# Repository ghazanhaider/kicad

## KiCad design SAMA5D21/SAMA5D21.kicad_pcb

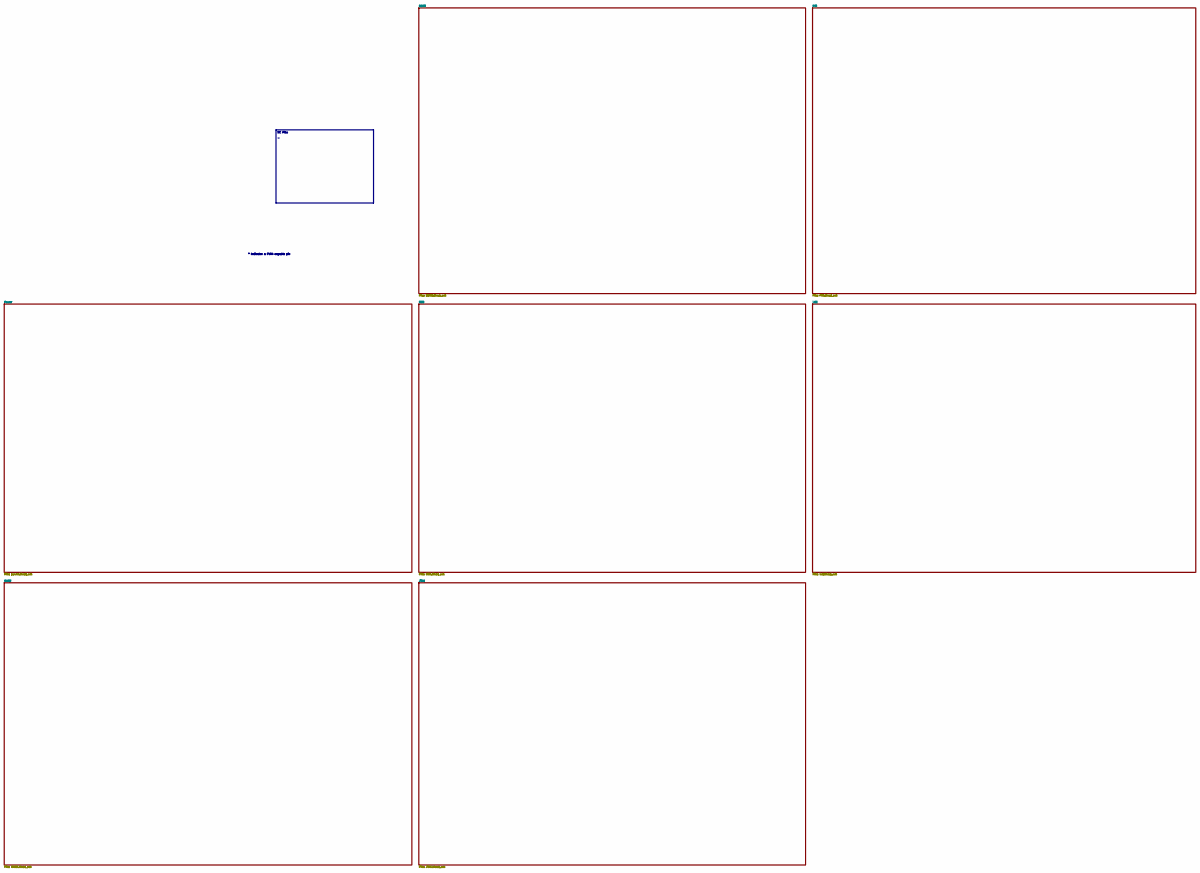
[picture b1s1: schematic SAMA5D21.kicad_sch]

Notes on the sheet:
NC Pins -
* Indicates a PWM-capable pin

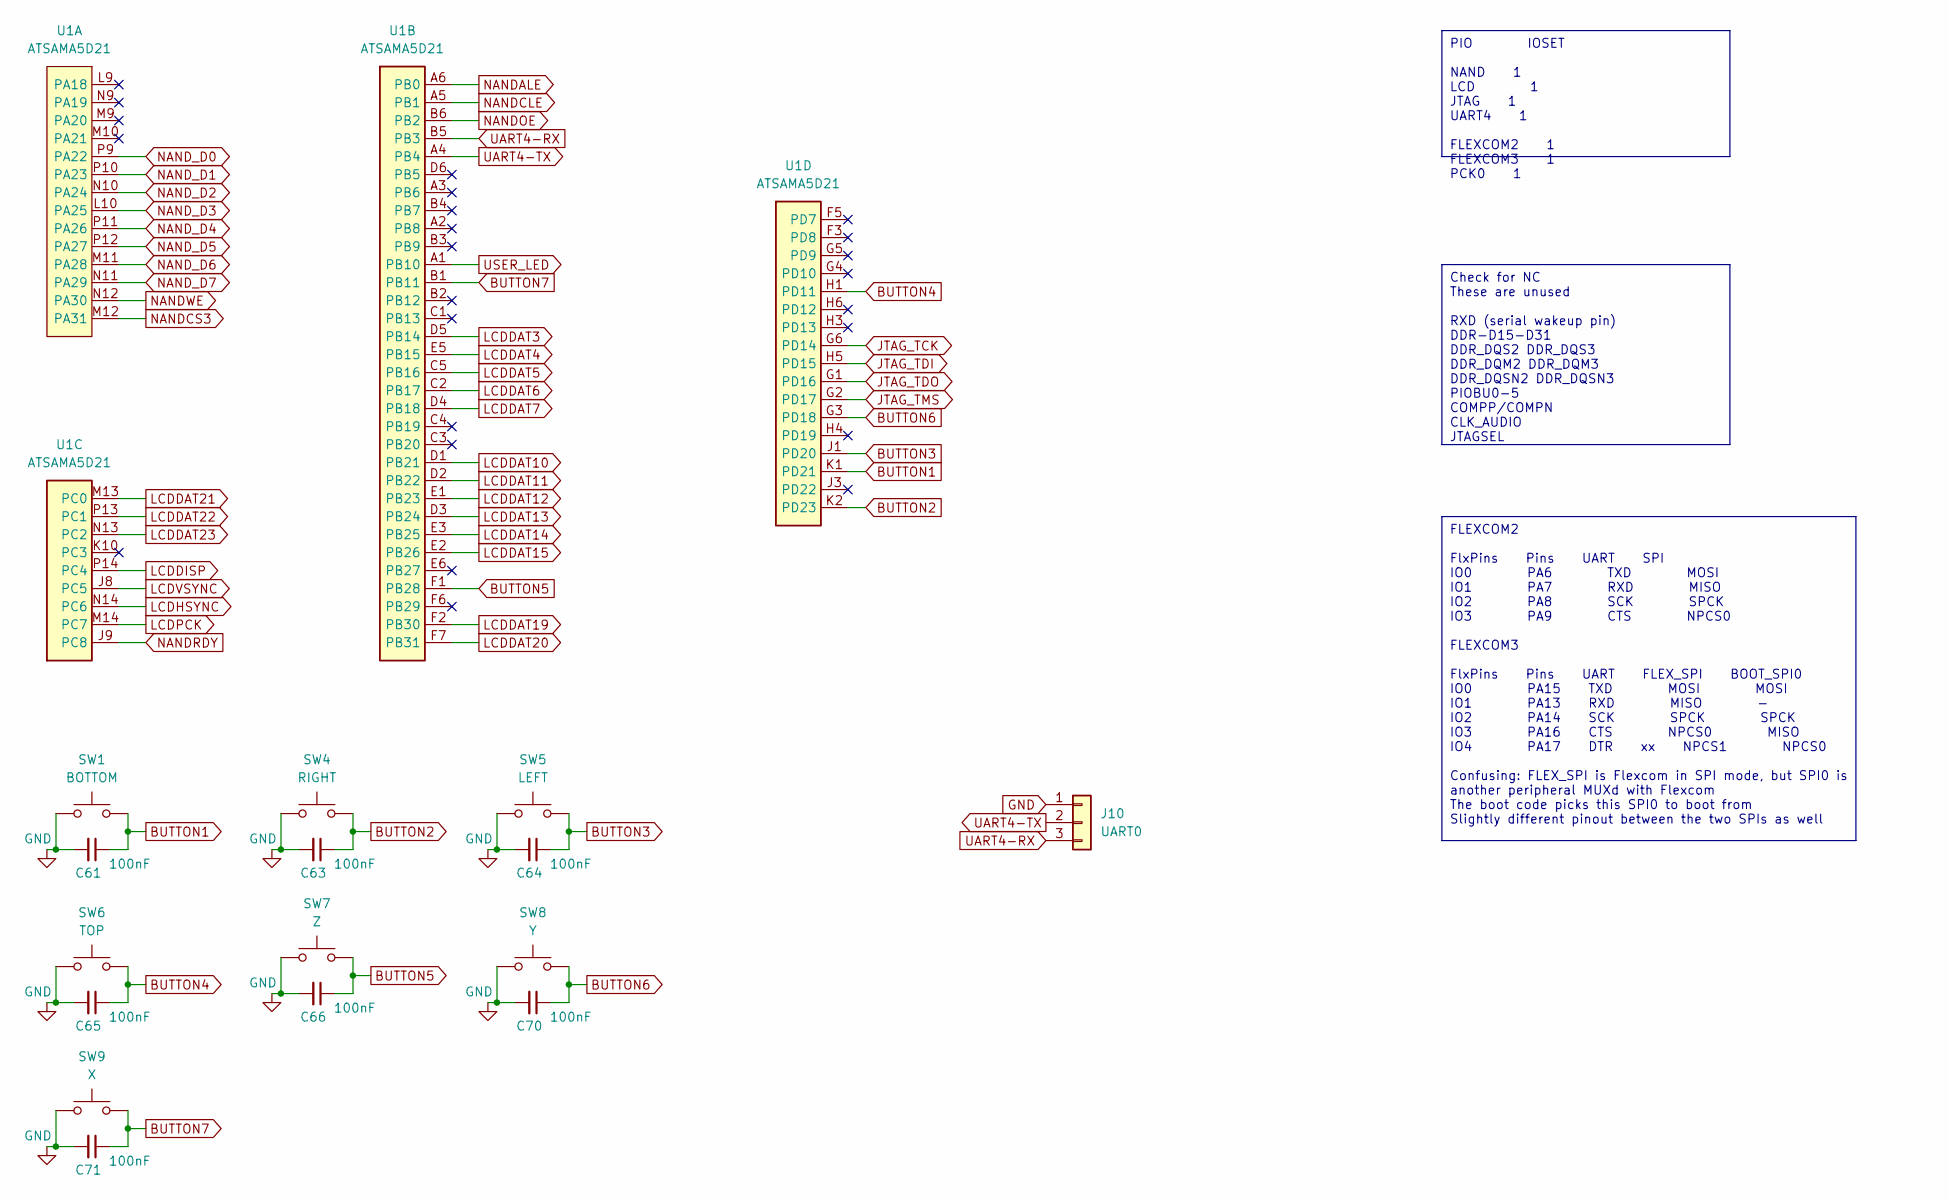
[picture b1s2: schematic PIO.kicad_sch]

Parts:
C61, C63, C64, C65, C66, C70, C71: 100nF; C_0603_1608Metric
J10: UART0; PinHeader_1x03_P1.27mm_Vertical
SW1: BOTTOM; SW_SPST_TL3305A
SW4: RIGHT; SW_SPST_TL3305A
SW5: LEFT; SW_SPST_TL3305A
SW6: TOP; SW_SPST_TL3305A
SW7: Z; SW_SPST_TL3305A
SW8: Y; SW_SPST_TL3305A
SW9: X; SW_SPST_TL3305A
U1: ATSAMA5D21; Microchip_TFBGA-196_11x11mm_Layout14x14_P0.75mm_SMD

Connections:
BUTTON1: C61.1, SW1.2, U1.K1 (PD21)
BUTTON2: C63.1, SW4.2, U1.K2 (PD23)
BUTTON3: C64.1, SW5.2, U1.J1 (PD20)
BUTTON4: C65.1, SW6.2, U1.H1 (PD11)
BUTTON5: C66.1, SW7.2, U1.F1 (PB28)
BUTTON6: C70.1, SW8.2, U1.G3 (PD18)
BUTTON7: C71.1, SW9.2, U1.B1 (PB11)
GNDADIOPLL: C61.2, C63.2, C64.2, C65.2, C66.2, C70.2, C71.2, J10.1, SW1.1, SW4.1, SW5.1, SW6.1, SW7.1, SW8.1, SW9.1; also elsewhere on the board
JTAG_TCK: U1.G6 (PD14); also elsewhere on the board
JTAG_TDI: U1.H5 (PD15); also elsewhere on the board
JTAG_TDO: U1.G1 (PD16); also elsewhere on the board
JTAG_TMS: U1.G2 (PD17); also elsewhere on the board
LCDDAT3: U1.D5 (PB14); also elsewhere on the board
LCDDAT4: U1.E5 (PB15); also elsewhere on the board
LCDDAT5: U1.C5 (PB16); also elsewhere on the board
LCDDAT6: U1.C2 (PB17); also elsewhere on the board
LCDDAT7: U1.D4 (PB18); also elsewhere on the board
LCDDAT10: U1.D1 (PB21); also elsewhere on the board
LCDDAT11: U1.D2 (PB22); also elsewhere on the board
LCDDAT12: U1.E1 (PB23); also elsewhere on the board
LCDDAT13: U1.D3 (PB24); also elsewhere on the board
LCDDAT14: U1.E3 (PB25); also elsewhere on the board
LCDDAT15: U1.E2 (PB26); also elsewhere on the board
LCDDAT19: U1.F2 (PB30); also elsewhere on the board
LCDDAT20: U1.F7 (PB31); also elsewhere on the board
LCDDAT21: U1.M13 (PC0); also elsewhere on the board
LCDDAT22: U1.P13 (PC1); also elsewhere on the board
LCDDAT23: U1.N13 (PC2); also elsewhere on the board
LCDDISP: U1.P14 (PC4); also elsewhere on the board
LCDHSYNC: U1.N14 (PC6); also elsewhere on the board
LCDPCK: U1.M14 (PC7); also elsewhere on the board
LCDVSYNC: U1.J8 (PC5); also elsewhere on the board
NANDALE: U1.A6 (PB0); also elsewhere on the board
NANDCLE: U1.A5 (PB1); also elsewhere on the board
NANDCS3: U1.M12 (PA31); also elsewhere on the board
NANDOE: U1.B6 (PB2); also elsewhere on the board
NANDRDY: U1.J9 (PC8); also elsewhere on the board
NANDWE: U1.N12 (PA30); also elsewhere on the board
NAND_D0: U1.P9 (PA22); also elsewhere on the board
NAND_D1: U1.P10 (PA23); also elsewhere on the board
NAND_D2: U1.N10 (PA24); also elsewhere on the board
NAND_D3: U1.L10 (PA25); also elsewhere on the board
NAND_D4: U1.P11 (PA26); also elsewhere on the board
NAND_D5: U1.P12 (PA27); also elsewhere on the board
NAND_D6: U1.M11 (PA28); also elsewhere on the board
NAND_D7: U1.N11 (PA29); also elsewhere on the board
UART4-RX: J10.3, U1.B5 (PB3)
UART4-TX: J10.2, U1.A4 (PB4)
USER_LED: U1.A1 (PB10); also elsewhere on the board

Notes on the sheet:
PIO IOSET NAND 1 LCD 1 JTAG 1 UART4 1 FLEXCOM2 1 FLEXCOM3 1 PCK0 1
Check for NC These are unused RXD (serial wakeup pin) DDR-D15-D31 DDR_DQS2 DDR_DQS3 DDR_DQM2 DDR_DQM3 DDR_DQSN2 DDR_DQSN3 PIOBU0-5 COMPP/COMPN CLK_AUDIO JTAGSEL
FLEXCOM2 FlxPins Pins UART SPI IO0 PA6 TXD MOSI IO1 PA7 RXD MISO IO2 PA8 SCK SPCK IO3 PA9 CTS NPCS0 FLEXCOM3 FlxPins Pins UART FLEX_SPI BOOT_SPI0 IO0 PA15 TXD MOSI MOSI IO1 PA13 RXD MISO - IO2 PA14 SCK SPCK SPCK IO3 PA16 CTS NPCS0 MISO IO4 PA17 DTR xx NPCS1 NPCS0 Confusing: FLEX_SPI is Flexcom in S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

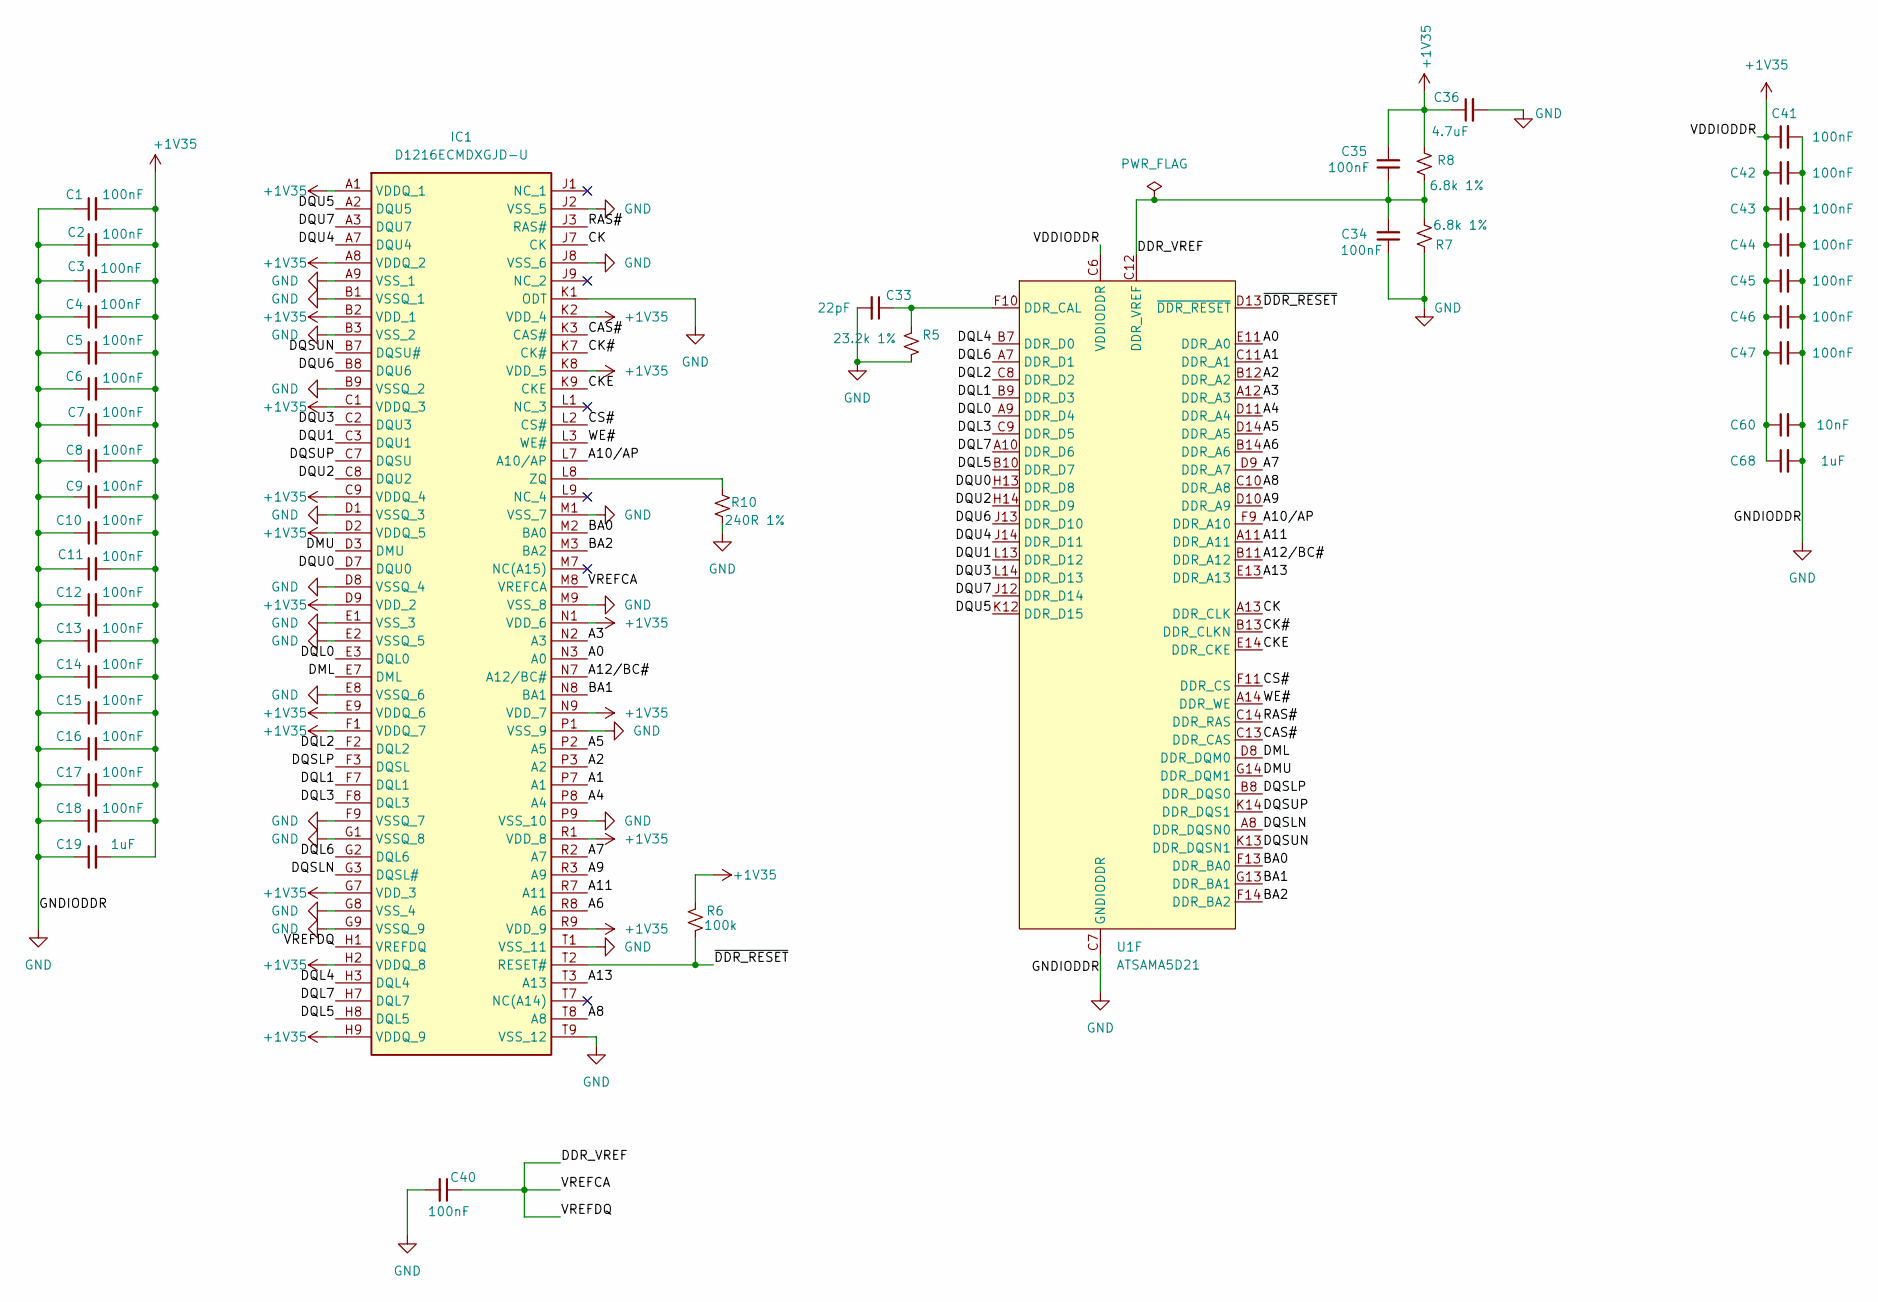
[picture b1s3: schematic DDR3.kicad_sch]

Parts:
C1, C2, C3, C4, C5, C6, C7, C8, C9, C10, C11, C12, C13, C14, C15, C16, C17, C18, C41, C42, C43, C44, C45, C46, C47: 100nF; C_0201_0603Metric
C19, C68: 1uF; C_0603_1608Metric
C33: 22pF; C_0603_1608Metric
C34, C35, C40: 100nF; C_0603_1608Metric
C36: 4.7uF; C_0603_1608Metric
C60: 10nF; C_0201_0603Metric
IC1: D1216ECMDXGJD-U; Micron_FBGA-96_7.5x13.5mm_Layout9x16_P0.8mm; Mouser Part Number D1216ECMDXGJD-U
R5: 23.2k 1%; R_0603_1608Metric
R6: 100k; R_0603_1608Metric
R7, R8: 6.8k 1%; R_0603_1608Metric
R10: 240R 1%; R_0402_1005Metric
U1: ATSAMA5D21; Microchip_TFBGA-196_11x11mm_Layout14x14_P0.75mm_SMD

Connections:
+1V35: C1.2, C2.2, C3.2, C4.2, C5.2, C6.2, C7.2, C8.2, C9.2, C10.2, C11.2, C12.2, C13.2, C14.2, C15.2, C16.2, C17.2, C18.2, C19.2, C35.2, C36.1, C41.1, C42.1, C43.1, C44.1, C45.1, C46.1, C47.1, C60.1, C68.1, IC1.A1 (VDDQ_1), IC1.A8 (VDDQ_2), IC1.B2 (VDD_1), IC1.C1 (VDDQ_3), IC1.C9 (VDDQ_4), IC1.D2 (VDDQ_5), IC1.D9 (VDD_2), IC1.E9 (VDDQ_6), IC1.F1 (VDDQ_7), IC1.G7 (VDD_3), IC1.H2 (VDDQ_8), IC1.H9 (VDDQ_9), IC1.K2 (VDD_4), IC1.K8 (VDD_5), IC1.N1 (VDD_6), IC1.N9 (VDD_7), IC1.R1 (VDD_8), IC1.R9 (VDD_9), R6.2, R8.1, U1.C6 (VDDIODDR), U1.E10 (VDDIODDR), U1.E12 (VDDIODDR), U1.G10 (VDDIODDR), U1.G12 (VDDIODDR), U1.H11 (VDDIODDR), U1.J10 (VDDIODDR); also elsewhere on the board
/DDR3/A0: IC1.N3 (A0), U1.E11 (DDR_A0)
/DDR3/A1: IC1.P7 (A1), U1.C11 (DDR_A1)
/DDR3/A2: IC1.P3 (A2), U1.B12 (DDR_A2)
/DDR3/A3: IC1.N2 (A3), U1.A12 (DDR_A3)
/DDR3/A4: IC1.P8 (A4), U1.D11 (DDR_A4)
/DDR3/A5: IC1.P2 (A5), U1.D14 (DDR_A5)
/DDR3/A6: IC1.R8 (A6), U1.B14 (DDR_A6)
/DDR3/A7: IC1.R2 (A7), U1.D9 (DDR_A7)
/DDR3/A8: IC1.T8 (A8), U1.C10 (DDR_A8)
/DDR3/A9: IC1.R3 (A9), U1.D10 (DDR_A9)
/DDR3/A10/AP: IC1.L7 (A10/AP), U1.F9 (DDR_A10)
/DDR3/A11: IC1.R7 (A11), U1.A11 (DDR_A11)
/DDR3/A12/BC#: IC1.N7 (A12/BC#), U1.B11 (DDR_A12)
/DDR3/A13: IC1.T3 (A13), U1.E13 (DDR_A13)
/DDR3/BA0: IC1.M2 (BA0), U1.F13 (DDR_BA0)
/DDR3/BA1: IC1.N8 (BA1), U1.G13 (DDR_BA1)
/DDR3/BA2: IC1.M3 (BA2), U1.F14 (DDR_BA2)
/DDR3/CAS#: IC1.K3 (CAS#), U1.C13 (DDR_CAS)
/DDR3/CK: IC1.J7 (CK), U1.A13 (DDR_CLK)
/DDR3/CK#: IC1.K7 (CK#), U1.B13 (DDR_CLKN)
/DDR3/CKE: IC1.K9 (CKE), U1.E14 (DDR_CKE)
/DDR3/CS#: IC1.L2 (CS#), U1.F11 (DDR_CS)
/DDR3/DDR_VREF: C34.2, C35.1, C40.1, IC1.H1 (VREFDQ), IC1.M8 (VREFCA), R7.1, R8.2, U1.C12 (DDR_VREF), U1.H12 (DDR_VREF)
/DDR3/DML: IC1.E7 (DML), U1.D8 (DDR_DQM0)
/DDR3/DMU: IC1.D3 (DMU), U1.G14 (DDR_DQM1)
/DDR3/DQL0: IC1.E3 (DQL0), U1.A9 (DDR_D4)
/DDR3/DQL1: IC1.F7 (DQL1), U1.B9 (DDR_D3)
/DDR3/DQL2: IC1.F2 (DQL2), U1.C8 (DDR_D2)
/DDR3/DQL3: IC1.F8 (DQL3), U1.C9 (DDR_D5)
/DDR3/DQL4: IC1.H3 (DQL4), U1.B7 (DDR_D0)
/DDR3/DQL5: IC1.H8 (DQL5), U1.B10 (DDR_D7)
/DDR3/DQL6: IC1.G2 (DQL6), U1.A7 (DDR_D1)
/DDR3/DQL7: IC1.H7 (DQL7), U1.A10 (DDR_D6)
/DDR3/DQSLN: IC1.G3 (DQSL#), U1.A8 (DDR_DQSN0)
/DDR3/DQSLP: IC1.F3 (DQSL), U1.B8 (DDR_DQS0)
/DDR3/DQSUN: IC1.B7 (DQSU#), U1.K13 (DDR_DQSN1)
/DDR3/DQSUP: IC1.C7 (DQSU), U1.K14 (DDR_DQS1)
/DDR3/DQU0: IC1.D7 (DQU0), U1.H13 (DDR_D8)
/DDR3/DQU1: IC1.C3 (DQU1), U1.L13 (DDR_D12)
/DDR3/DQU2: IC1.C8 (DQU2), U1.H14 (DDR_D9)
/DDR3/DQU3: IC1.C2 (DQU3), U1.L14 (DDR_D13)
/DDR3/DQU4: IC1.A7 (DQU4), U1.J14 (DDR_D11)
/DDR3/DQU5: IC1.A2 (DQU5), U1.K12 (DDR_D15)
/DDR3/DQU6: IC1.B8 (DQU6), U1.J13 (DDR_D10)
/DDR3/DQU7: IC1.A3 (DQU7), U1.J12 (DDR_D14)
/DDR3/RAS#: IC1.J3 (RAS#), U1.C14 (DDR_RAS)
/DDR3/WE#: IC1.L3 (WE#), U1.A14 (DDR_WE)
/DDR3/~DDR_RESET: IC1.T2 (RESET#), R6.1, U1.D13 (~DDR_RESET)
GNDADIOPLL: C1.1, C2.1, C3.1, C4.1, C5.1, C6.1, C7.1, C8.1, C9.1, C10.1, C11.1, C12.1, C13.1, C14.1, C15.1, C16.1, C17.1, C18.1, C19.1, C33.2, C34.1, C36.2, C40.2, C41.2, C42.2, C43.2, C44.2, C45.2, C46.2, C47.2, C60.2, C68.2, IC1.A9 (VSS_1), IC1.B1 (VSSQ_1), IC1.B3 (VSS_2), IC1.B9 (VSSQ_2), IC1.D1 (VSSQ_3), IC1.D8 (VSSQ_4), IC1.E1 (VSS_3), IC1.E2 (VSSQ_5), IC1.E8 (VSSQ_6), IC1.F9 (VSSQ_7), IC1.G1 (VSSQ_8), IC1.G8 (VSS_4), IC1.G9 (VSSQ_9), IC1.J2 (VSS_5), IC1.J8 (VSS_6), IC1.K1 (ODT), IC1.M1 (VSS_7), IC1.M9 (VSS_8), IC1.P1 (VSS_9), IC1.P9 (VSS_10), IC1.T1 (VSS_11), IC1.T9 (VSS_12), R5.1, R7.2, R10.2, U1.C7 (GNDIODDR), U1.D12 (GNDIODDR), U1.E9 (GNDIODDR), U1.F12 (GNDIODDR), U1.G11 (GNDIODDR), U1.H10 (GNDIODDR), U1.J11 (GNDIODDR); also elsewhere on the board
unnamed: IC1.L8 (ZQ), R10.1
unnamed: C33.1, R5.2, U1.F10 (DDR_CAL)

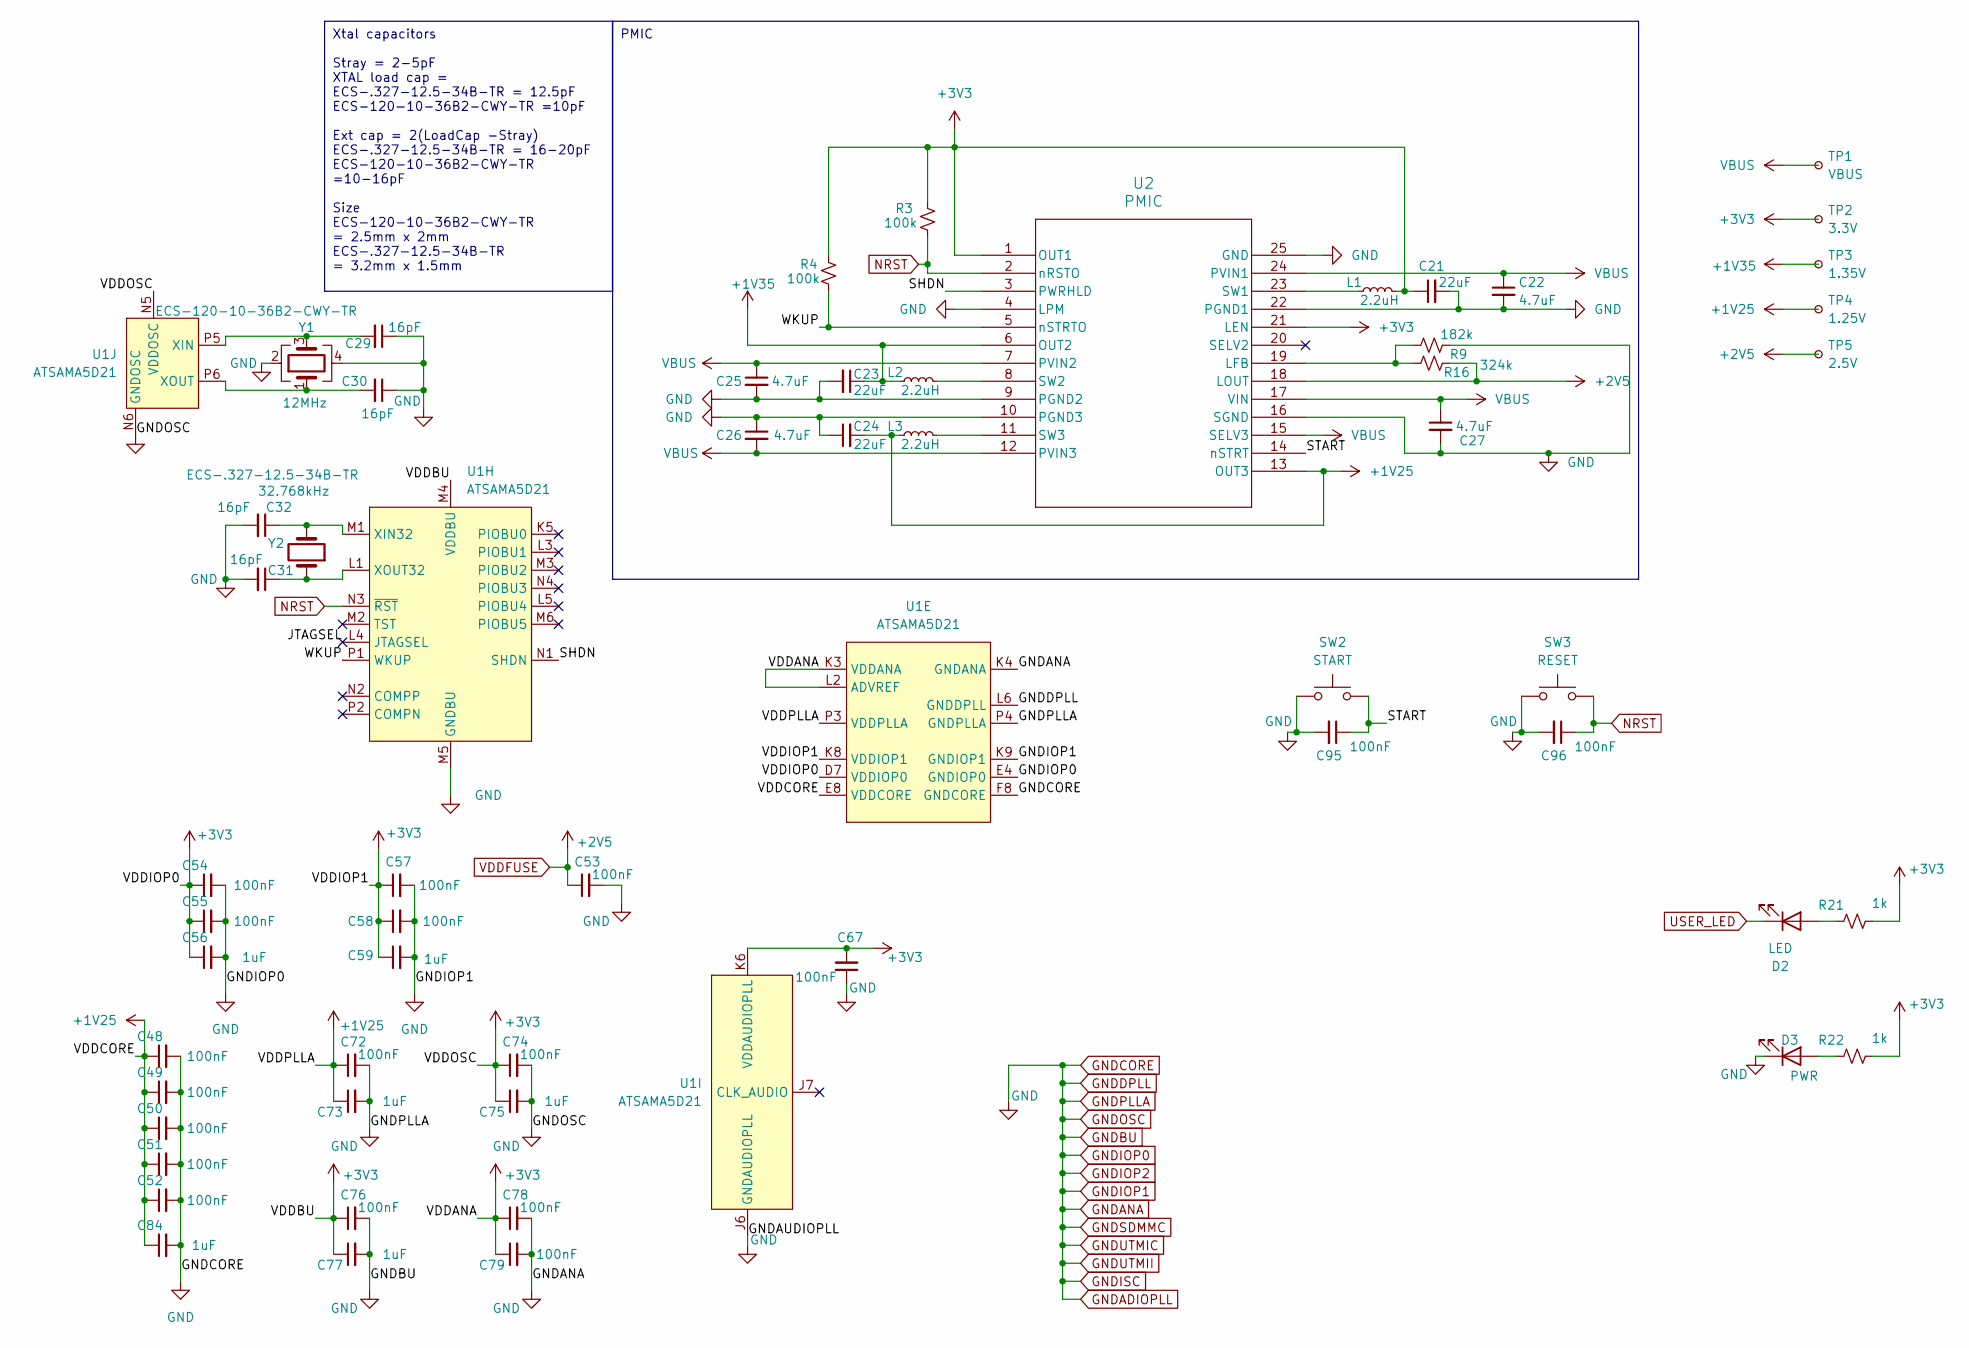
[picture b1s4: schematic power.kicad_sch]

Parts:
C21, C23, C24: 22uF; C_0603_1608Metric
C22, C25, C26, C27: 4.7uF; C_0603_1608Metric
C29, C30, C31, C32: 16pF; C_0603_1608Metric
C48, C49, C50, C51, C52, C53, C54, C55, C57, C58, C67, C72, C74, C76, C78, C79: 100nF; C_0201_0603Metric
C56, C59, C73, C75, C77, C84: 1uF; C_0201_0603Metric
C95, C96: 100nF; C_0603_1608Metric
D2: LED; LED_0805_2012Metric
D3: PWR; LED_0805_2012Metric
L1, L2, L3: 2.2uH; L_Wurth_WE-LQSH-2512
R3, R4: 100k; R_0603_1608Metric
R9: 182k; R_0603_1608Metric
R16: 324k; R_0603_1608Metric
R21, R22: 1k; R_0603_1608Metric
SW2: START; SW_SPST_TL3305A
SW3: RESET; SW_SPST_TL3305A
TP1: VBUS; TestPoint_Pad_D1.0mm
TP2: 3.3V; TestPoint_Pad_D1.0mm
TP3: 1.35V; TestPoint_Pad_D1.0mm
TP4: 1.25V; TestPoint_Pad_D1.0mm
TP5: 2.5V; TestPoint_Pad_D1.0mm
U1: ATSAMA5D21; Microchip_TFBGA-196_11x11mm_Layout14x14_P0.75mm_SMD
U2: PMIC; VQFN24_RMB_MCH
Y1: 12MHz; Crystal_SMD_2520-4Pin_2.5x2.0mm
Y2: 32.768kHz; Crystal_SMD_3215-2Pin_3.2x1.5mm

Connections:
+1V25: C24.2, C48.1, C49.1, C50.1, C51.1, C52.1, C72.1, C73.1, C84.1, L3.1, TP4.1, U1.E8 (VDDCORE), U1.G8 (VDDCORE), U1.H8 (VDDCORE), U1.H9 (VDDCORE), U1.J5 (VDDCORE), U1.P3 (VDDPLLA), U2.13 (OUT3); also elsewhere on the board
+1V35: C23.1, L2.1, TP3.1, U2.6 (OUT2); also elsewhere on the board
+3V3: C21.1, C54.1, C55.1, C56.1, C57.1, C58.1, C59.1, C67.2, C74.1, C75.1, C76.1, C77.1, C78.1, C79.1, L1.2, R3.2, R4.2, R21.1, R22.1, TP2.1, U1.D7 (VDDIOP0), U1.F4 (VDDIOP0), U1.H2 (VDDANA), U1.K3 (VDDANA), U1.K6 (VDDAUDIOPLL), U1.K8 (VDDIOP1), U1.L2 (ADVREF), U1.L11 (VDDIOP1), U1.M4 (VDDBU), U1.N5 (VDDOSC), U2.1 (OUT1), U2.21 (LEN); also elsewhere on the board
/Power/JTAGSEL: U1.L4 (JTAGSEL)
/Power/SHDN: U1.N1 (SHDN), U2.3 (PWRHLD)
/Power/START: C95.1, SW2.2, U2.14 (nSTRT)
/Power/WKUP: R4.1, U1.P1 (WKUP), U2.5 (nSTRTO)
GNDADIOPLL: C21.2, C22.2, C23.2, C24.1, C25.2, C26.1, C27.2, C29.1, C30.1, C31.2, C32.2, C48.2, C49.2, C50.2, C51.2, C52.2, C53.2, C54.2, C55.2, C56.2, C57.2, C58.2, C59.2, C67.1, C72.2, C73.2, C74.2, C75.2, C76.2, C77.2, C78.2, C79.2, C84.2, C95.2, C96.2, D3.1 (K), R9.2, SW2.1, SW3.1, U1.E4 (GNDIOP0), U1.E7 (GNDIOP0), U1.F8 (GNDCORE), U1.G7 (GNDCORE), U1.G9 (GNDCORE), U1.H7 (GNDCORE), U1.J2 (GNDANA), U1.J4 (GNDCORE), U1.J6 (GNDAUDIOPLL), U1.K4 (GNDANA), U1.K9 (GNDIOP1), U1.L6 (GNDDPLL), U1.L12 (GNDIOP1), U1.M5 (GNDBU), U1.N6 (GNDOSC), U1.P4 (GNDPLLA), U2.4 (LPM), U2.9 (PGND2), U2.10 (PGND3), U2.16 (SGND), U2.22 (PGND1), U2.25 (GND), Y1.2, Y1.4; also elsewhere on the board
NRST: C96.1, R3.1, SW3.2, U1.N3 (~RST), U2.2 (nRSTO); also elsewhere on the board
unnamed: D2.2 (A), R21.2
unnamed: D3.2 (A), R22.2
unnamed: C32.1, U1.M1 (XIN32), Y2.2
unnamed: C31.1, U1.L1 (XOUT32), Y2.1
unnamed: C29.2, U1.P5 (XIN), Y1.3
unnamed: C30.2, U1.P6 (XOUT), Y1.1
unnamed: R9.1, R16.2, U2.19 (LFB)
unnamed: L1.1, U2.23 (SW1)
unnamed: L2.2, U2.8 (SW2)
unnamed: L3.2, U2.11 (SW3)
USER_LED: D2.1 (K); also elsewhere on the board
VBUS: C22.1, C25.1, C26.2, C27.1, TP1.1, U2.7 (PVIN2), U2.12 (PVIN3), U2.15 (SELV3), U2.17 (VIN), U2.24 (PVIN1); also elsewhere on the board
VDDFUSE: C53.1, R16.1, TP5.1, U2.18 (LOUT); also elsewhere on the board

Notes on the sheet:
PMIC
Xtal capacitors Stray = 2-5pF XTAL load cap = ECS-.327-12.5-34B-TR = 12.5pF ECS-120-10-36B2-CWY-TR =10pF Ext cap = 2(LoadCap -Stray) ECS-.327-12.5-34B-TR = 16-20pF ECS-120-10-36B2-CWY-TR =10-16pF Size ECS-120-10-36B2-CWY-TR = 2.5mm x 2mm ECS-.327-12.5-34B-TR = 3.2mm x 1.5mm

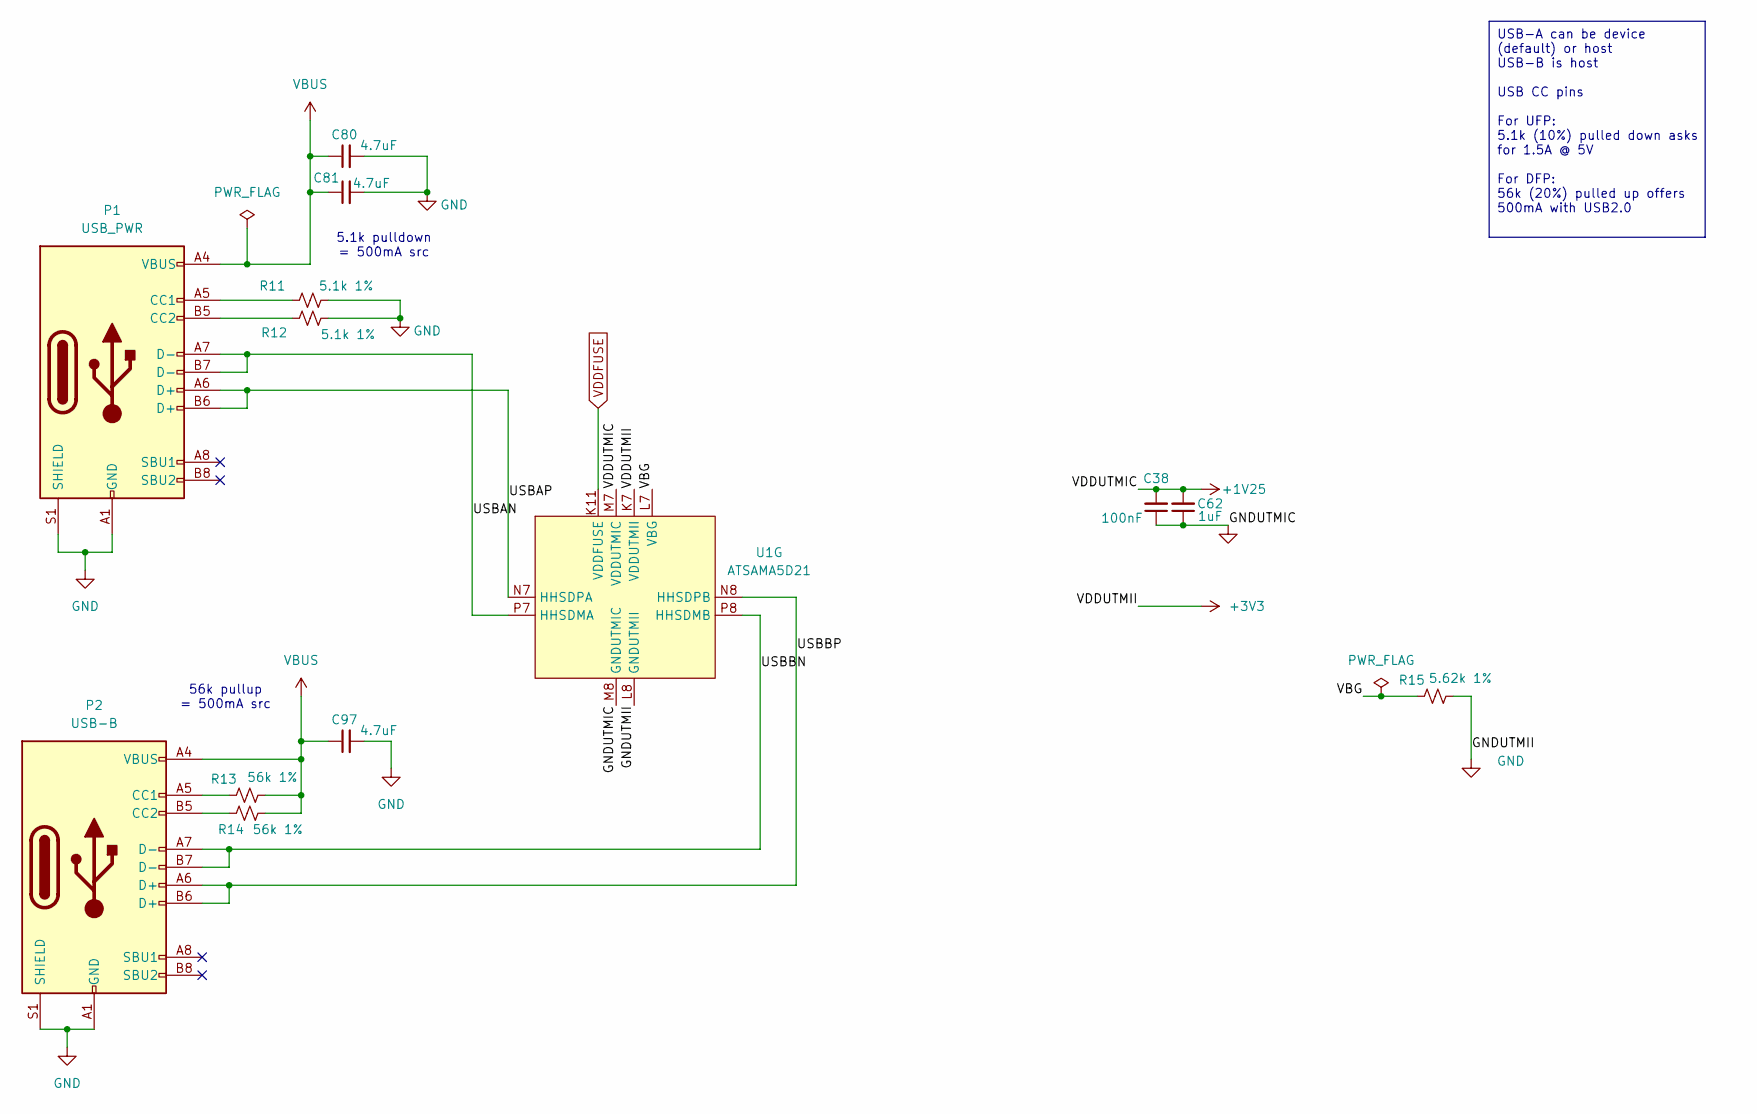
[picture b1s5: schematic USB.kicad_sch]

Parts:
C38: 100nF; C_0201_0603Metric
C62: 1uF; C_0201_0603Metric
C80, C81, C97: 4.7uF; C_0603_1608Metric
P1: USB_PWR; USB_C_Receptacle_GCT_USB4105-xx-A_16P_TopMnt_Horizontal
P2: USB-B; USB_C_Receptacle_GCT_USB4105-xx-A_16P_TopMnt_Horizontal
R11, R12: 5.1k 1%; R_0603_1608Metric
R13, R14: 56k 1%; R_0603_1608Metric
R15: 5.62k 1%; R_0201_0603Metric
U1: ATSAMA5D21; Microchip_TFBGA-196_11x11mm_Layout14x14_P0.75mm_SMD

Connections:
+1V25: C38.2, C62.2, U1.M7 (VDDUTMIC); also elsewhere on the board
+3V3: U1.K7 (VDDUTMII); also elsewhere on the board
/USB/USBAN: P1.A7 (D-), P1.B7 (D-), U1.P7 (HHSDMA)
/USB/USBAP: P1.A6 (D+), P1.B6 (D+), U1.N7 (HHSDPA)
/USB/USBBN: P2.A7 (D-), P2.B7 (D-), U1.P8 (HHSDMB)
/USB/USBBP: P2.A6 (D+), P2.B6 (D+), U1.N8 (HHSDPB)
/USB/VBG: R15.2, U1.L7 (VBG)
GNDADIOPLL: C38.1, C62.1, C80.2, C81.2, C97.2, P1.A1 (GND), P1.A12 (GND), P1.B1 (GND), P1.B12 (GND), P1.S1 (SHIELD), P2.A1 (GND), P2.A12 (GND), P2.B1 (GND), P2.B12 (GND), P2.S1 (SHIELD), R11.1, R12.1, R15.1, U1.L8 (GNDUTMII), U1.M8 (GNDUTMIC); also elsewhere on the board
unnamed: P1.A5 (CC1), R11.2
unnamed: P1.B5 (CC2), R12.2
unnamed: P2.A5 (CC1), R13.2
unnamed: P2.B5 (CC2), R14.2
VBUS: C80.1, C81.1, C97.1, P1.A4 (VBUS), P1.A9 (VBUS), P1.B4 (VBUS), P1.B9 (VBUS), P2.A4 (VBUS), P2.A9 (VBUS), P2.B4 (VBUS), P2.B9 (VBUS), R13.1, R14.1; also elsewhere on the board
VDDFUSE: U1.K11 (VDDFUSE); also elsewhere on the board

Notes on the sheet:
USB-A can be device (default) or host USB-B is host USB CC pins For UFP: 5.1k (10%) pulled down asks for 1.5A @ 5V For DFP: 56k (20%) pulled up offers 500mA with USB2.0
56k pullup = 500mA src
5.1k pulldown = 500mA src

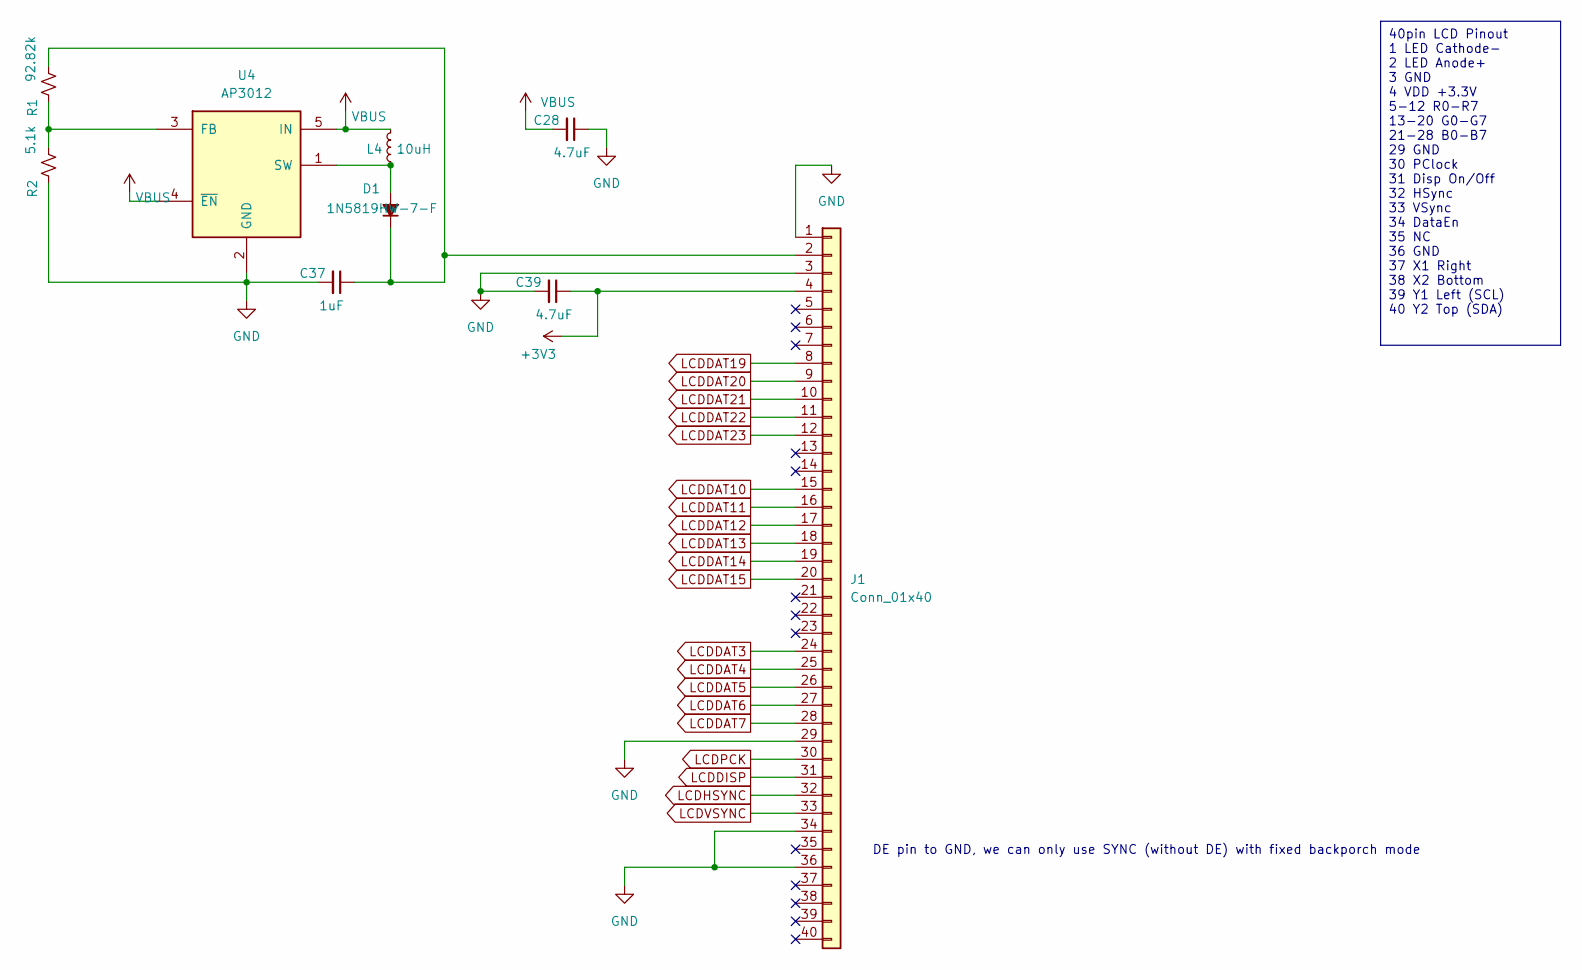
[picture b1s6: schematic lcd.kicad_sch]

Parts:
C28, C39: 4.7uF; C_0603_1608Metric
C37: 1uF; C_0603_1608Metric
D1: 1N5819HW-7-F; D_SOD-123
J1: Conn_01x40; Hirose_FH12-40S-0.5SH_1x40-1MP_P0.50mm_Horizontal
L4: 10uH; L_Wurth_WE-LQSH-2512
R1: 92.82k; R_0603_1608Metric
R2: 5.1k; R_0603_1608Metric
U4: AP3012; SOT-23-5

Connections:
+3V3: C39.1, J1.4; also elsewhere on the board
GNDADIOPLL: C28.1, C37.2, C39.2, J1.1, J1.3, J1.29, J1.34, J1.36, R2.2, U4.2 (GND); also elsewhere on the board
LCDDAT3: J1.24; also elsewhere on the board
LCDDAT4: J1.25; also elsewhere on the board
LCDDAT5: J1.26; also elsewhere on the board
LCDDAT6: J1.27; also elsewhere on the board
LCDDAT7: J1.28; also elsewhere on the board
LCDDAT10: J1.15; also elsewhere on the board
LCDDAT11: J1.16; also elsewhere on the board
LCDDAT12: J1.17; also elsewhere on the board
LCDDAT13: J1.18; also elsewhere on the board
LCDDAT14: J1.19; also elsewhere on the board
LCDDAT15: J1.20; also elsewhere on the board
LCDDAT19: J1.8; also elsewhere on the board
LCDDAT20: J1.9; also elsewhere on the board
LCDDAT21: J1.10; also elsewhere on the board
LCDDAT22: J1.11; also elsewhere on the board
LCDDAT23: J1.12; also elsewhere on the board
LCDDISP: J1.31; also elsewhere on the board
LCDHSYNC: J1.32; also elsewhere on the board
LCDPCK: J1.30; also elsewhere on the board
LCDVSYNC: J1.33; also elsewhere on the board
unnamed: D1.2 (A), L4.1, U4.1 (SW)
unnamed: C37.1, D1.1 (K), J1.2, R1.1
unnamed: R1.2, R2.1, U4.3 (FB)
VBUS: C28.2, L4.2, U4.4 (~EN), U4.5 (IN); also elsewhere on the board

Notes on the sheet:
40pin LCD Pinout 1 LED Cathode- 2 LED Anode+ 3 GND 4 VDD +3.3V 5-12 R0-R7 13-20 G0-G7 21-28 B0-B7 29 GND 30 PClock 31 Disp On/Off 32 HSync 33 VSync 34 DataEn 35 NC 36 GND 37 X1 Right 38 X2 Bottom 39 Y1 Left (SCL) 40 Y2 Top (SDA)
DE pin to GND, we can only use SYNC (without DE) with fixed backporch mode
